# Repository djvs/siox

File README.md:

# siox

PSIO SIO-X switchboard redone in kicad.  Not 100% sure this is correct yet.  Credit to Voultar for original basic design.

I'm using this successfully in my PS1 (SCPH-1001) for PSIO, mod chip stuff (left half of the board) is untested.

U1 has to be manually rotated (for now) if you print this through JLCPCB.  Indicator dot should be in the top left.  Mod chip is not included but socket is available as in the original SIO-X.

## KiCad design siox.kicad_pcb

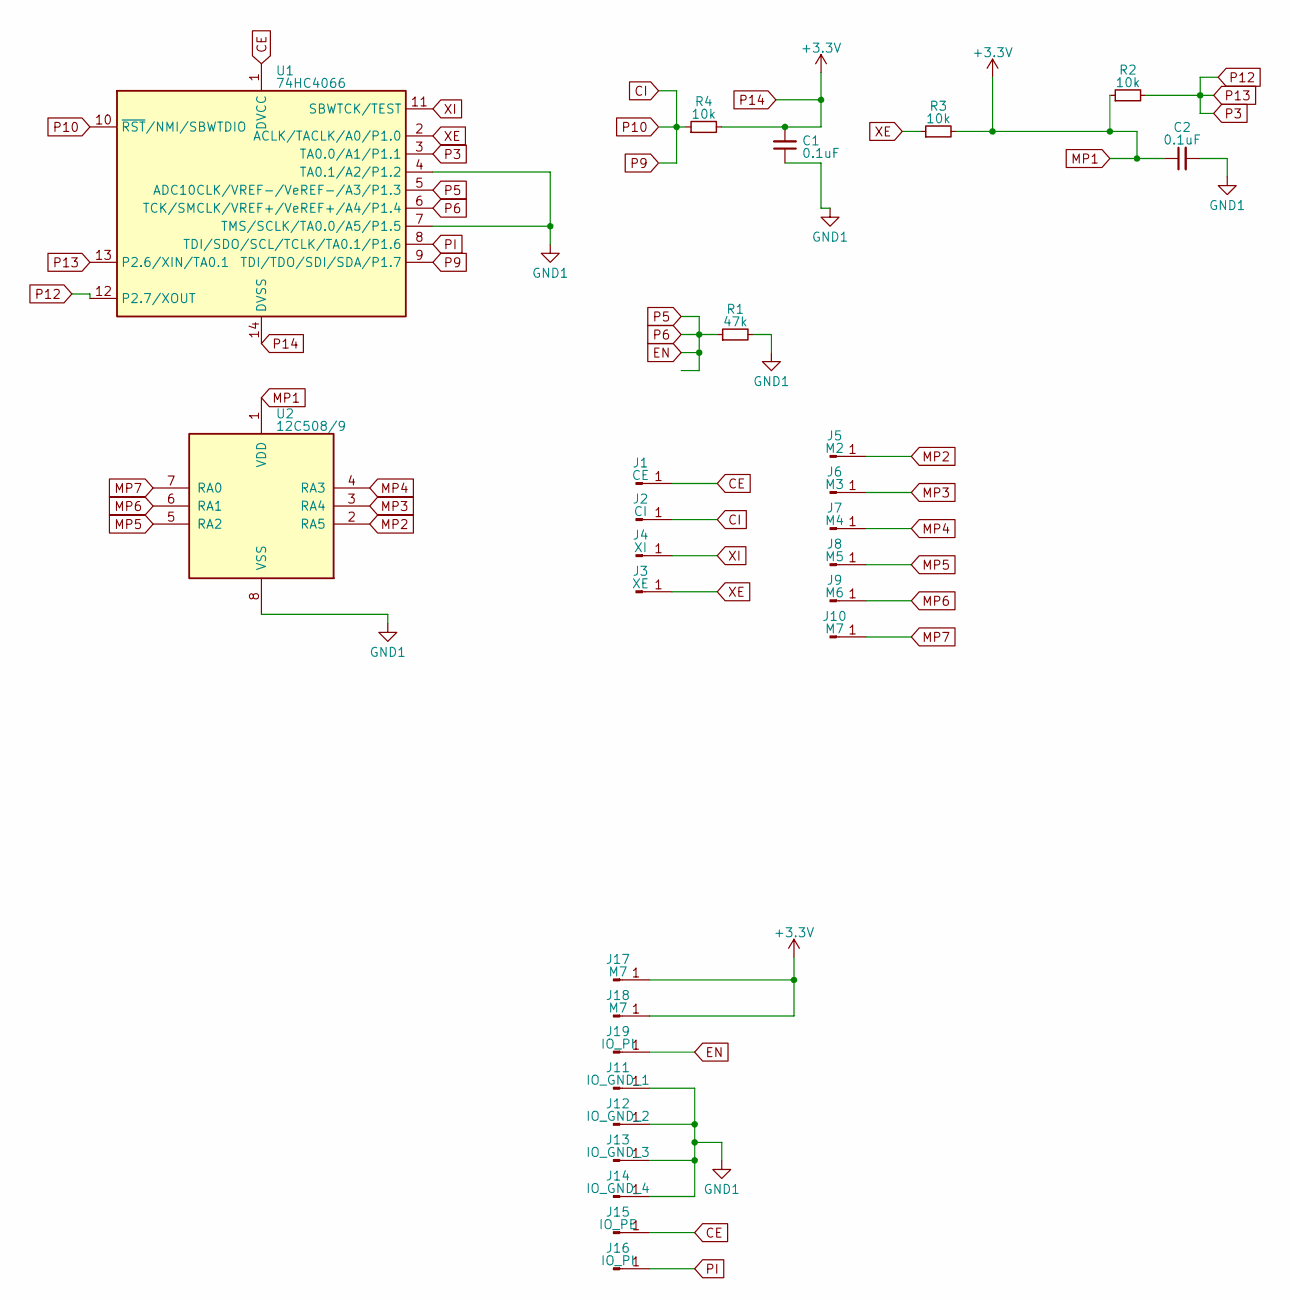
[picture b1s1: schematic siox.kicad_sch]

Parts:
C1, C2: 0.1uF; C_0805_2012Metric
J1: CE; TestPoint_Pad_D2.0mm
J2: CI; TestPoint_Pad_D2.0mm
J3: XE; TestPoint_Pad_D2.0mm
J4: XI; TestPoint_Pad_D2.0mm
J5: M2; TestPoint_Pad_D2.0mm
J6: M3; TestPoint_Pad_D2.0mm
J7: M4; TestPoint_Pad_D2.0mm
J8: M5; TestPoint_Pad_D2.0mm
J9: M6; TestPoint_Pad_D2.0mm
J10: M7; TestPoint_Pad_D2.0mm
J11: IO_GND_1; PsioPin
J12: IO_GND_2; PsioPin
J13: IO_GND_3; PsioPin
J14: IO_GND_4; PsioPin
J15: IO_PE; PsioPin
J16, J19: IO_PI; PsioPin
J17, J18: M7; PsioPin
R1: 47k; R_0805_2012Metric
R2, R3, R4: 10k; R_0805_2012Metric
U1: 74HC4066; TSSOP-14_4.4x5mm_P0.65mm
U2: 12C508/9; SOP-8_5.28x5.23mm_P1.27mm

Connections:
CE: J1.1, J15.1, U1.1 (DVCC)
CI: J2.1, R4.1, U1.9 (TDI/TDO/SDI/SDA/P1.7), U1.10 (~RST/NMI/SBWTDIO)
EN: J19.1, R1.1, U1.5 (ADC10CLK/VREF-/VeREF-/A3/P1.3), U1.6 (TCK/SMCLK/VREF+/VeREF+/A4/P1.4)
GND1: C1.1, C2.2, J11.1, J12.1, J13.1, J14.1, R1.2, U1.4 (TA0.1/A2/P1.2), U1.7 (TMS/SCLK/TA0.0/A5/P1.5), U2.8 (VSS)
MP1: C1.2, C2.1, J17.1, J18.1, R2.1, R3.2, R4.2, U1.14 (DVSS), U2.1 (VDD)
MP2: J5.1, U2.2 (RA5)
MP3: J6.1, U2.3 (RA4)
MP4: J7.1, U2.4 (RA3)
MP5: J8.1, U2.5 (RA2)
MP6: J9.1, U2.6 (RA1)
MP7: J10.1, U2.7 (RA0)
P12: R2.2, U1.3 (TA0.0/A1/P1.1), U1.12 (P2.7/XOUT), U1.13 (P2.6/XIN/TA0.1)
PI: J16.1, U1.8 (TDI/SDO/SCL/TCLK/TA0.1/P1.6)
XE: J3.1, R3.1, U1.2 (ACLK/TACLK/A0/P1.0)
XI: J4.1, U1.11 (SBWTCK/TEST)

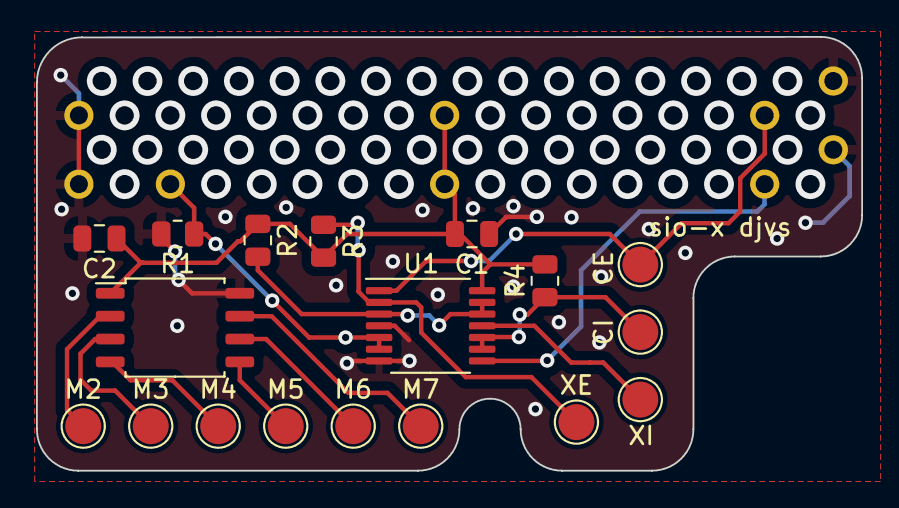
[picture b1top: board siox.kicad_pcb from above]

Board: 2 copper layers, 45.8 x 24.1 mm, 27 parts (0 on the bottom side), 15 nets.

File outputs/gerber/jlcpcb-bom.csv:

Comment,Footprint,Designator,JLCPCB Part #（optional )
"CE","TestPoint_Pad_D2.0mm","J1"
"0.1uF","C_0805_2012Metric","C2,C1","C49678"
"10k","R_0805_2012Metric","R2,R4,R3","C17414"
"M7","TestPoint_Pad_D2.0mm","J10"
"M7","PsioPin","J18,J17"
"M4","TestPoint_Pad_D2.0mm","J7"
"IO_PI","PsioPin","J16,J19"
"M2","TestPoint_Pad_D2.0mm","J5"
"M3","TestPoint_Pad_D2.0mm","J6"
"IO_GND_2","PsioPin","J12"
"74HC4066","TSSOP-14_4.4x5mm_P0.65mm","U1","C5650"
"12C508/9","SOP-8_5.28x5.23mm_P1.27mm","U2"
"M5","TestPoint_Pad_D2.0mm","J8"
"XE","TestPoint_Pad_D2.0mm","J3"
"IO_GND_3","PsioPin","J13"
"IO_GND_1","PsioPin","J11"
"47k","R_0805_2012Metric","R1"
"M6","TestPoint_Pad_D2.0mm","J9"
"XI","TestPoint_Pad_D2.0mm","J4"
"IO_PE","PsioPin","J15"
"IO_GND_4","PsioPin","J14"
"CI","TestPoint_Pad_D2.0mm","J2"

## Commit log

2022-12-18 fixes
2022-12-18 cleanup
2022-12-18 fix pads
2022-12-18 readme
